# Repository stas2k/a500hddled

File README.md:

# a500hddled - A500 keyboard HDD LED mod

This repo contains Kicad sources for a board to light up the Disk LED on keyboard on HDD activity.

It is useful to users having an internal HDD controller.

## Design

The circuit implements the same schematic as the original A500 FDD LED circuit.

## Board production

I use JLCPCB with the following options:
* PCB Thickness: 1.2

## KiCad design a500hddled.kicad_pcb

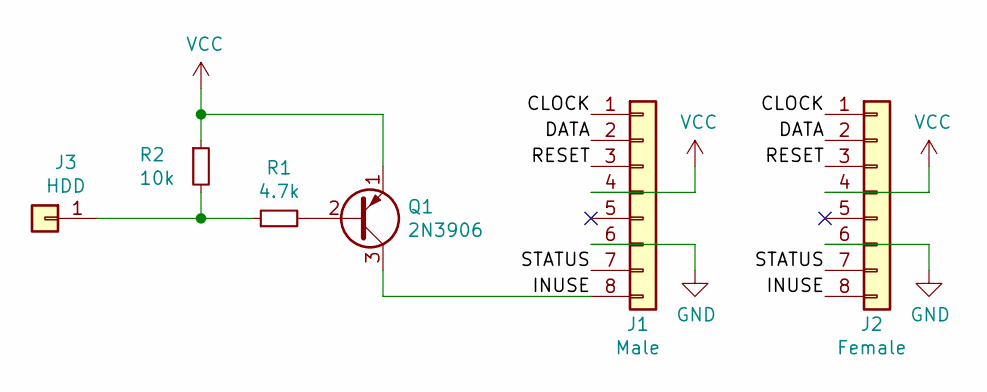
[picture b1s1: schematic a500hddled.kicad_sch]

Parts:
J1: Male; PinHeader_1x08_P2.54mm_Vertical
J2: Female; PinSocket_1x08_P2.54mm_Vertical
J3: HDD; PinHeader_1x01_P2.54mm_Horizontal
Q1: 2N3906; TO-92_Inline
R1: 4.7k; R_Axial_DIN0207_L6.3mm_D2.5mm_P10.16mm_Horizontal
R2: 10k; R_Axial_DIN0207_L6.3mm_D2.5mm_P10.16mm_Horizontal

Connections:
/CLOCK: J1.1, J2.1
/DATA: J1.2, J2.2
/INUSE: J1.8, J2.8, Q1.3 (C)
/RESET: J1.3, J2.3
/STATUS: J1.7, J2.7
GND: J1.6, J2.6
unnamed: J3.1, R1.1, R2.2
unnamed: Q1.2 (B), R1.2
VCC: J1.4, J2.4, Q1.1 (E), R2.1

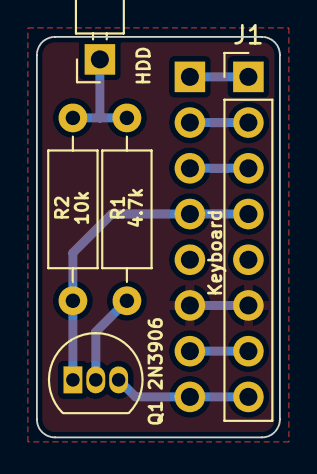
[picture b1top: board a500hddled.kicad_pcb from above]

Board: 2 copper layers, 13.5 x 22.2 mm, 6 parts (1 on the bottom side), 9 nets.

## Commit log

2021-07-16 add 3D models, upgrade kicad
2021-07-16 Add board image to README.md
